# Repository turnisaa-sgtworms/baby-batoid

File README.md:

# baby-batoid
 baby (8u) version of Kotte's Batoid keeb

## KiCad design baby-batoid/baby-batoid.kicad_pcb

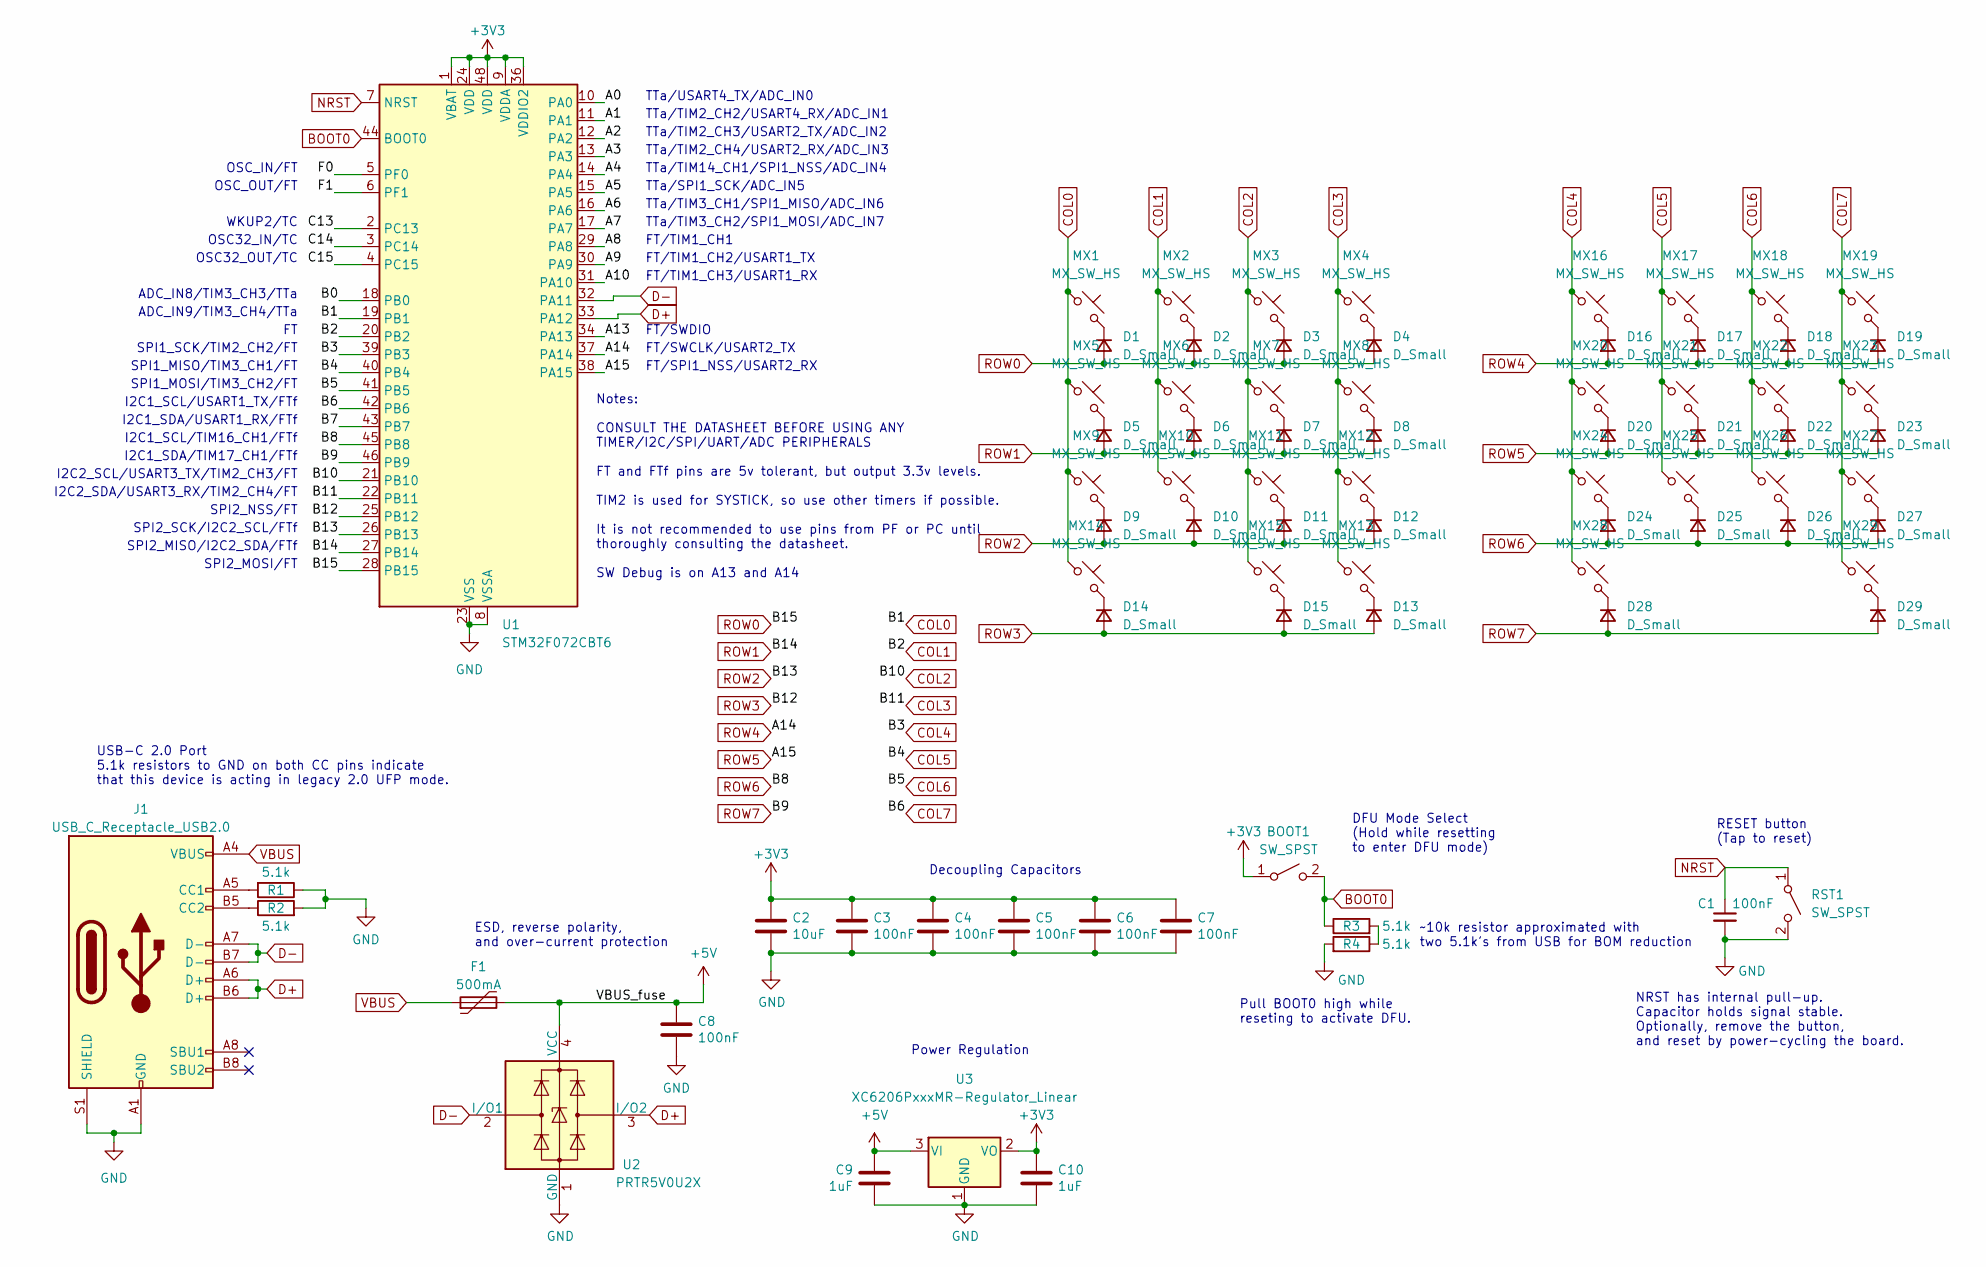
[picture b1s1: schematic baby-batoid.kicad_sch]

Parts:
BOOT1: SW_SPST; SW_SPST_TL3342
C1, C3, C4, C5, C6, C7, C8: 100nF; C_0402_1005Metric; LCSC C307331
C2: 10uF; C_0603_1608Metric; LCSC C307331
C9, C10: 1uF; C_0402_1005Metric; LCSC C307331
D1, D2, D3, D4, D5, D6, D7, D8, D9, D10, D11, D12, D13, D14, D15, D16, D17, D18, D19, D20, D21, D22, D23, D24, D25, D26, D27, D28, D29: D_Small; D_SOD-123
F1: 500mA; Fuse_1206_3216Metric; LCSC C135341
J1: USB_C_Receptacle_USB2.0; USB_C_Receptacle_HRO_TYPE-C-31-M-12; JlcRotOffset 180
MX1, MX2, MX3, MX4, MX5, MX6, MX7, MX8, MX9, MX10, MX11, MX12, MX13, MX14, MX15, MX16, MX17, MX18, MX19, MX20, MX21, MX22, MX23, MX24, MX25, MX26, MX27, MX28, MX29: MX_SW_HS; SW_MX_HS_CPG151101S11_1u
R1, R2, R3, R4: 5.1k; R_0402_1005Metric
RST1: SW_SPST; SW_SPST_TL3342
U1: STM32F072CBT6; LQFP-48_7x7mm_P0.5mm; JlcRotOffset 90
U2: PRTR5V0U2X; SOT-143; LCSC C2827688
U3: XC6206PxxxMR-Regulator_Linear; SOT-23; LCSC C5446

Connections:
+3V3: BOOT1.1 (A), C2.1, C3.1, C4.1, C5.1, C6.1, C7.1, C10.1, U1.1 (VBAT), U1.9 (VDDA), U1.24 (VDD), U1.36 (VDDIO2), U1.48 (VDD), U3.2 (VO)
+5V: C8.1, C9.1, F1.2, U2.4 (VCC), U3.3 (VI)
/A0: U1.10 (PA0)
/A1: U1.11 (PA1)
/A2: U1.12 (PA2)
/A3: U1.13 (PA3)
/A4: U1.14 (PA4)
/A5: U1.15 (PA5)
/A6: U1.16 (PA6)
/A7: U1.17 (PA7)
/A8: U1.29 (PA8)
/A9: U1.30 (PA9)
/A10: U1.31 (PA10)
/A13: U1.34 (PA13)
/B0: U1.18 (PB0)
/B7: U1.43 (PB7)
/C13: U1.2 (PC13)
/C14: U1.3 (PC14)
/C15: U1.4 (PC15)
/F0: U1.5 (PF0)
/F1: U1.6 (PF1)
BOOT0: BOOT1.2 (B), R3.1, U1.44 (BOOT0)
COL0: MX1.1, MX5.1, MX9.1, MX14.1, U1.19 (PB1)
COL1: MX2.1, MX6.1, MX10.1, U1.20 (PB2)
COL2: MX3.1, MX7.1, MX11.1, MX15.1, U1.21 (PB10)
COL3: MX4.1, MX8.1, MX12.1, MX13.1, U1.22 (PB11)
COL4: MX16.1, MX20.1, MX24.1, MX28.1, U1.39 (PB3)
COL5: MX17.1, MX21.1, MX25.1, U1.40 (PB4)
COL6: MX18.1, MX22.1, MX26.1, U1.41 (PB5)
COL7: MX19.1, MX23.1, MX27.1, MX29.1, U1.42 (PB6)
D+: J1.A6 (D+), J1.B6 (D+), U1.33 (PA12), U2.3 (I/O2)
D-: J1.A7 (D-), J1.B7 (D-), U1.32 (PA11), U2.2 (I/O1)
GND: C1.2, C2.2, C3.2, C4.2, C5.2, C6.2, C7.2, C8.2, C9.2, C10.2, J1.A1 (GND), J1.A12 (GND), J1.B1 (GND), J1.B12 (GND), J1.S1 (SHIELD), R1.1, R2.2, R4.2, RST1.2 (B), U1.8 (VSSA), U1.23 (VSS), U1.35 (VSS), U1.47 (VSS), U2.1 (GND), U3.1 (GND)
NRST: C1.1, RST1.1 (A), U1.7 (NRST)
unnamed: D1.1 (K), MX1.2
unnamed: D2.1 (K), MX2.2
unnamed: D3.1 (K), MX3.2
unnamed: D4.1 (K), MX4.2
unnamed: D5.1 (K), MX5.2
unnamed: D6.1 (K), MX6.2
unnamed: D7.1 (K), MX7.2
unnamed: D8.1 (K), MX8.2
unnamed: D9.1 (K), MX9.2
unnamed: D10.1 (K), MX10.2
unnamed: D11.1 (K), MX11.2
unnamed: D12.1 (K), MX12.2
unnamed: D13.1 (K), MX13.2
unnamed: D14.1 (K), MX14.2
unnamed: D15.1 (K), MX15.2
unnamed: D16.1 (K), MX16.2
unnamed: D17.1 (K), MX17.2
unnamed: D18.1 (K), MX18.2
unnamed: D19.1 (K), MX19.2
unnamed: D20.1 (K), MX20.2
unnamed: D21.1 (K), MX21.2
unnamed: D22.1 (K), MX22.2
unnamed: D23.1 (K), MX23.2
unnamed: D24.1 (K), MX24.2
unnamed: D25.1 (K), MX25.2
unnamed: D26.1 (K), MX26.2
unnamed: D27.1 (K), MX27.2
unnamed: D28.1 (K), MX28.2
unnamed: D29.1 (K), MX29.2
unnamed: J1.A5 (CC1), R1.2
unnamed: J1.B5 (CC2), R2.1
unnamed: R3.2, R4.1
ROW0: D1.2 (A), D2.2 (A), D3.2 (A), D4.2 (A), U1.28 (PB15)
ROW1: D5.2 (A), D6.2 (A), D7.2 (A), D8.2 (A), U1.27 (PB14)
ROW2: D9.2 (A), D10.2 (A), D11.2 (A), D12.2 (A), U1.26 (PB13)
ROW3: D13.2 (A), D14.2 (A), D15.2 (A), U1.25 (PB12)
ROW4: D16.2 (A), D17.2 (A), D18.2 (A), D19.2 (A), U1.37 (PA14)
ROW5: D20.2 (A), D21.2 (A), D22.2 (A), D23.2 (A), U1.38 (PA15)
ROW6: D24.2 (A), D25.2 (A), D26.2 (A), D27.2 (A), U1.45 (PB8)
ROW7: D28.2 (A), D29.2 (A), U1.46 (PB9)
VBUS: F1.1, J1.A4 (VBUS), J1.A9 (VBUS), J1.B4 (VBUS), J1.B9 (VBUS)

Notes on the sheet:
SPI1_SCK/TIM2_CH2/FT
FT/TIM1_CH1
FT/TIM1_CH3/USART1_RX
SPI2_NSS/FT
Notes: CONSULT THE DATASHEET BEFORE USING ANY TIMER/I2C/SPI/UART/ADC PERIPHERALS FT and FTf pins are 5v tolerant, but output 3.3v levels. TIM2 is used for SYSTICK, so use other timers if possible. It is not recommended to use pins from PF or PC until thoroughly consulting the datasheet. SW Debug is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
TTa/TIM2_CH4/USART2_RX/ADC_IN3
NRST has internal pull-up. Capacitor holds signal stable. Optionally, remove the button, and reset by power-cycling the board.
FT/SWDIO
Decoupling Capacitors
SPI1_MOSI/TIM3_CH2/FT
ADC_IN9/TIM3_CH4/TTa
I2C2_SCL/USART3_TX/TIM2_CH3/FT
SPI2_MISO/I2C2_SDA/FTf
FT/SWCLK/USART2_TX
I2C1_SCL/TIM16_CH1/FTf
~10k resistor approximated with two 5.1k's from USB for BOM reduction
TTa/TIM2_CH2/USART4_RX/ADC_IN1
USB-C 2.0 Port 5.1k resistors to GND on both CC pins indicate that this device is acting in legacy 2.0 UFP mode.
TTa/TIM2_CH3/USART2_TX/ADC_IN2
OSC_IN/FT
DFU Mode Select (Hold while resetting to enter DFU mode)
WKUP2/TC
I2C2_SDA/USART3_RX/TIM2_CH4/FT
ADC_IN8/TIM3_CH3/TTa
RESET button (Tap to reset)
Pull BOOT0 high while reseting to activate DFU.
I2C1_SDA/TIM17_CH1/FTf
TTa/SPI1_SCK/ADC_IN5
TTa/TIM3_CH1/SPI1_MISO/ADC_IN6
TTa/TIM3_CH2/SPI1_MOSI/ADC_IN7
OSC32_OUT/TC
FT/SPI1_NSS/USART2_RX
SPI1_MISO/TIM3_CH1/FT
OSC32_IN/TC
TTa/TIM14_CH1/SPI1_NSS/ADC_IN4
I2C1_SDA/USART1_RX/FTf
SPI2_MOSI/FT
FT/TIM1_CH2/USART1_TX
Power Regulation
SPI2_SCK/I2C2_SCL/FTf

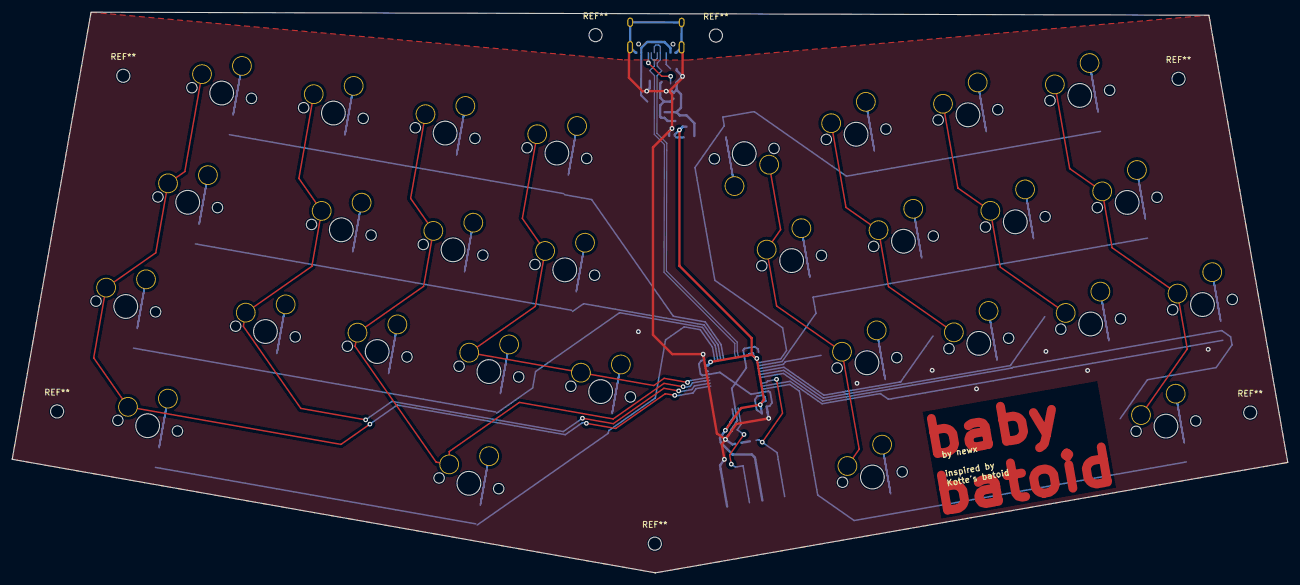
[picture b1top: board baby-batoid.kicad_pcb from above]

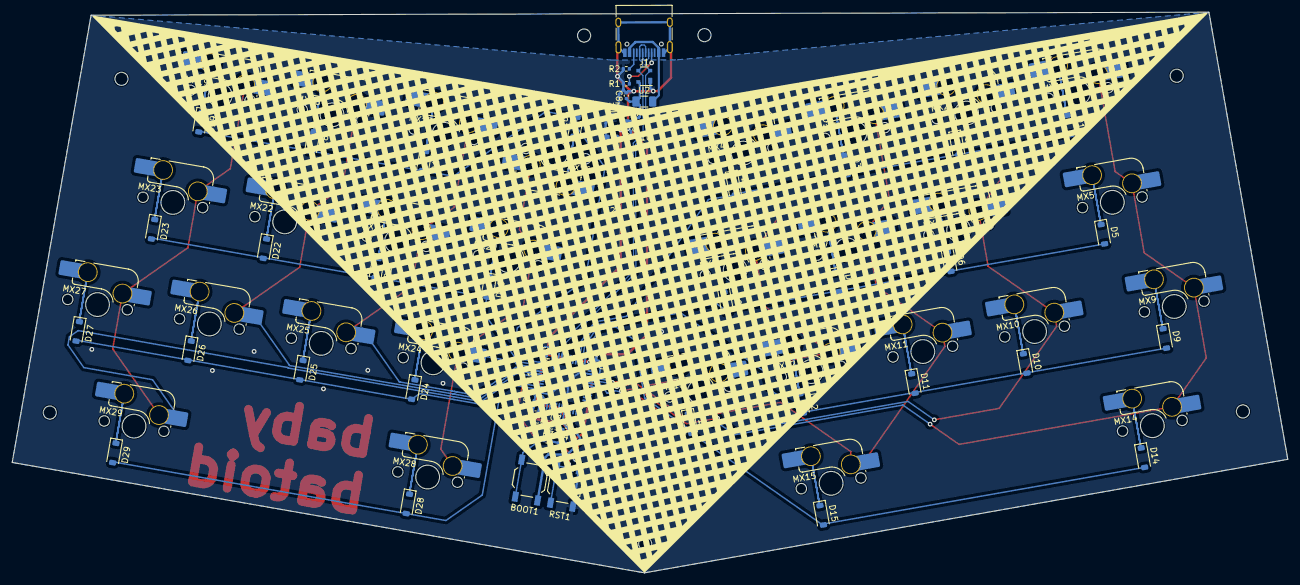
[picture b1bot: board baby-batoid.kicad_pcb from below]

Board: 2 copper layers, 214.1 x 94.1 mm, 79 parts (79 on the bottom side), 56 nets.

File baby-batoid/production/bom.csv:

Designator,Footprint,Quantity,Value,LCSC Part #
"BOOT1, RST1",SW_SPST_TL3342,2,SW_SPST,
"C1, C3, C4, C5, C6, C7, C8",0402,7,100nF,C307331
"C10, C9",0402,2,1uF,C307331
C2,0603,1,10uF,C307331
"D1, D10, D11, D12, D13, D14, D15, D16, D17, D18, D19, D2, D20, D21, D22, D23, D24, D25, D26, D27, D28, D29, D3, D4, D5, D6, D7, D8, D9",D_SOD-123,29,D_Small,
F1,1206,1,500mA,C135341
J1,USB_C_Receptacle_HRO_TYPE-C-31-M-12,1,USB_C_Receptacle_USB2.0,
"MX1, MX10, MX11, MX12, MX13, MX14, MX15, MX16, MX17, MX18, MX19, MX2, MX20, MX21, MX22, MX23, MX24, MX25, MX26, MX27, MX28, MX29, MX3, MX4, MX6, MX7, MX8",SW_MX_HS_CPG151101S11_1u,27,MX_SW_HS,
MX5,SW_MX_HS_CPG151101S11_1.75u,1,MX_SW_HS,
MX9,SW_MX_HS_CPG151101S11_1.5u,1,MX_SW_HS,
"R1, R2, R3, R4",0402,4,5.1k,
U1,LQFP-48_7x7mm_P0.5mm,1,STM32F072CBT6,
U2,SOT-143,1,PRTR5V0U2X,C2827688
U3,SOT-23,1,XC6206PxxxMR-Regulator_Linear,C5446

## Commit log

2025-03-08 built baby batoid :D
2025-03-09 production file work
2025-03-12 cleaned up left routing, need to do right still
2025-03-12 finished cleaning routing up
2025-03-12 finished routing, finalized BOM, new .step
2025-03-13 added case STLs for printing
